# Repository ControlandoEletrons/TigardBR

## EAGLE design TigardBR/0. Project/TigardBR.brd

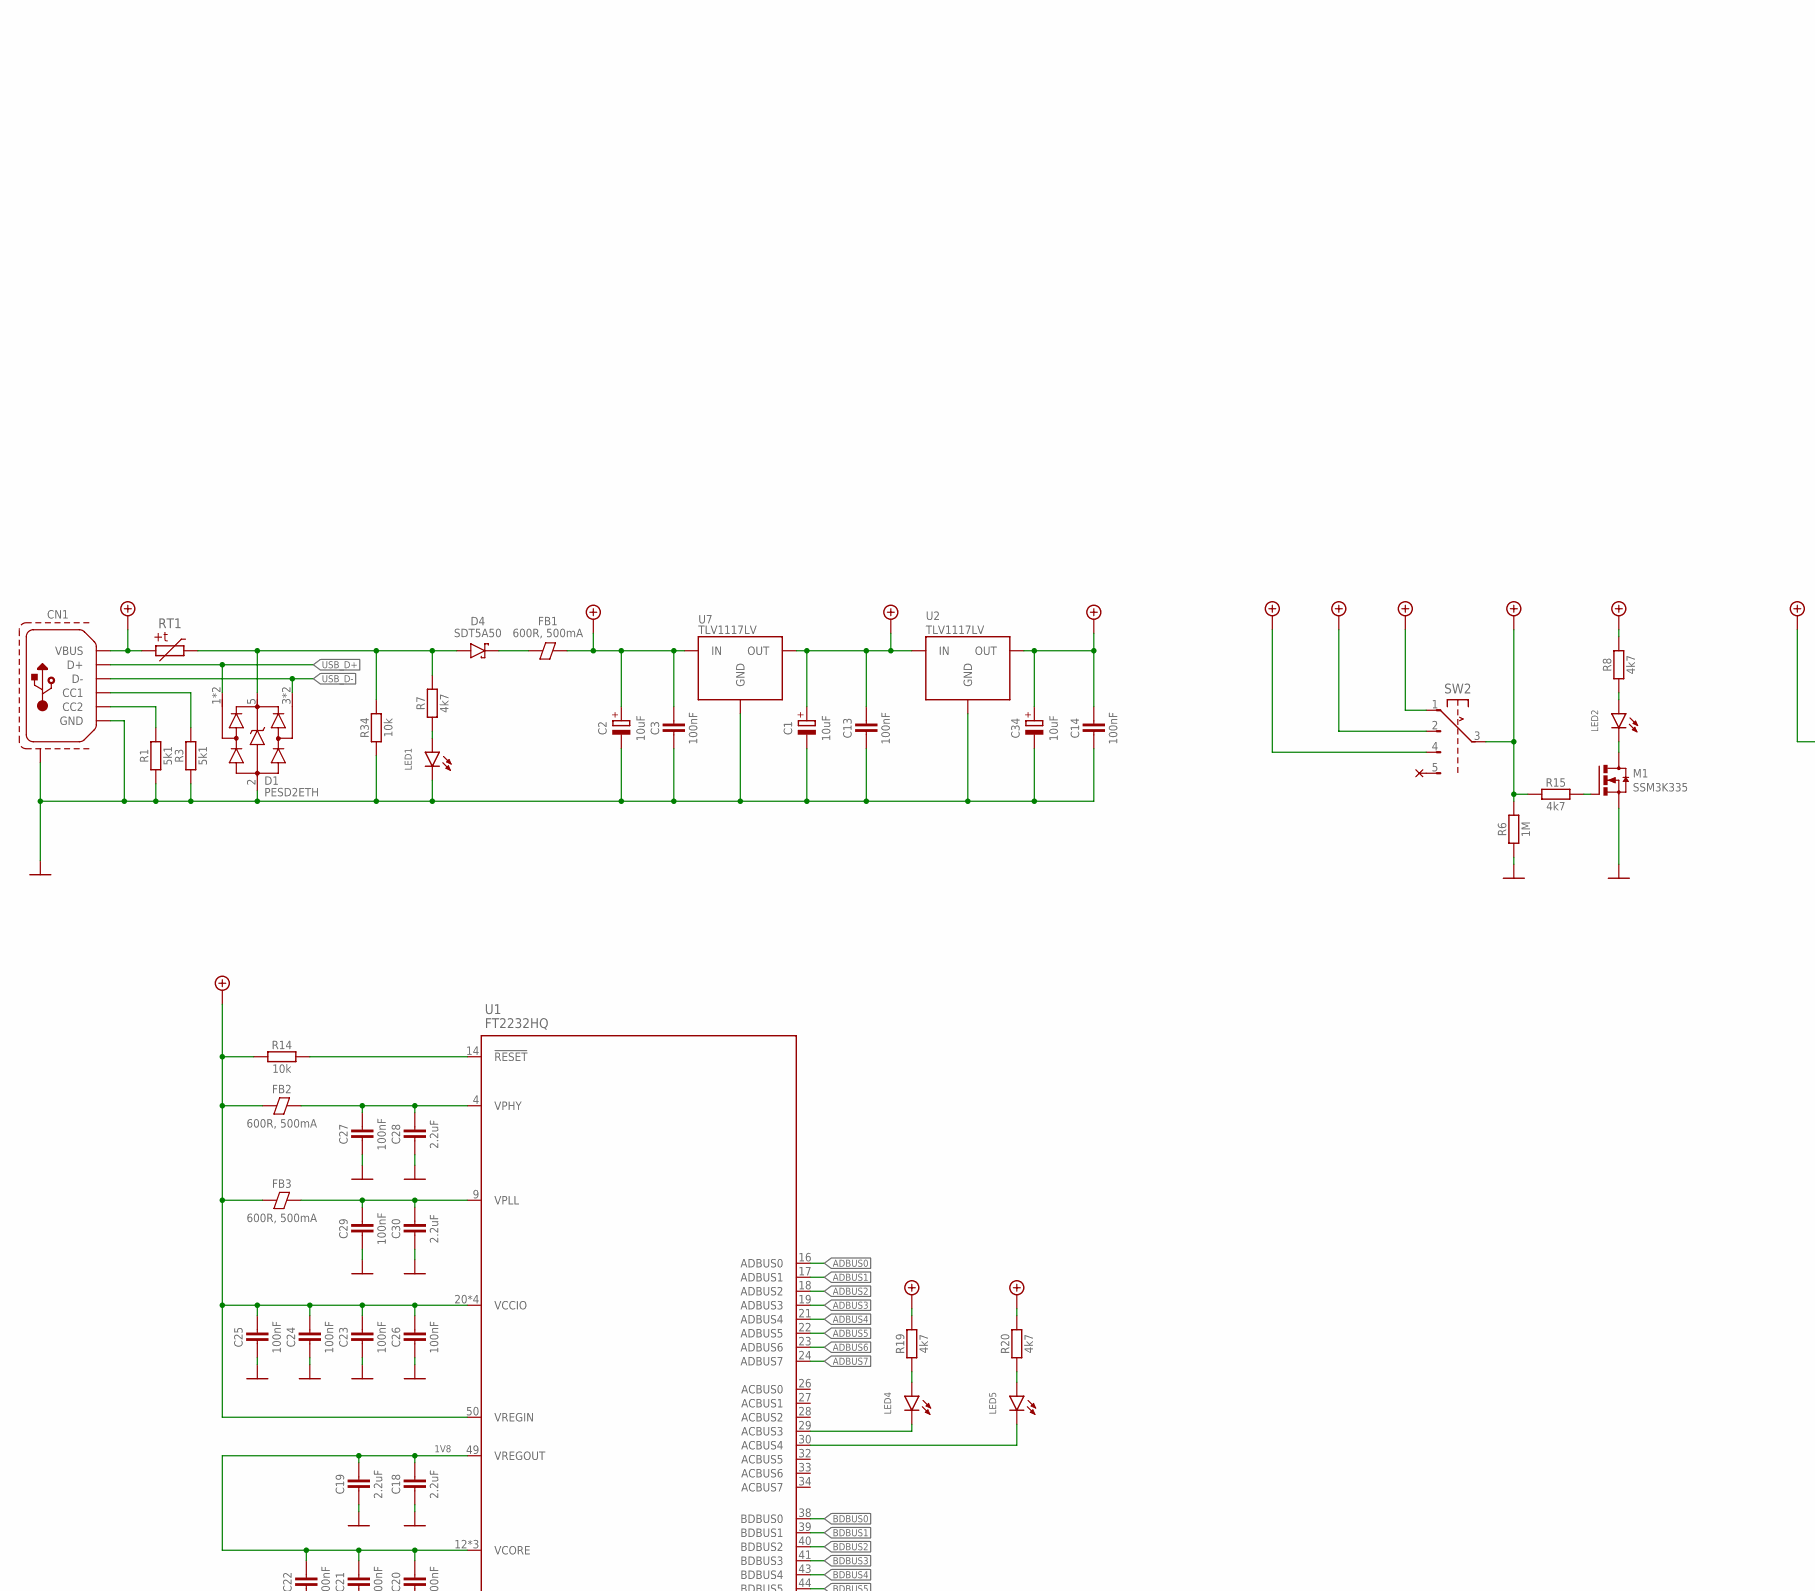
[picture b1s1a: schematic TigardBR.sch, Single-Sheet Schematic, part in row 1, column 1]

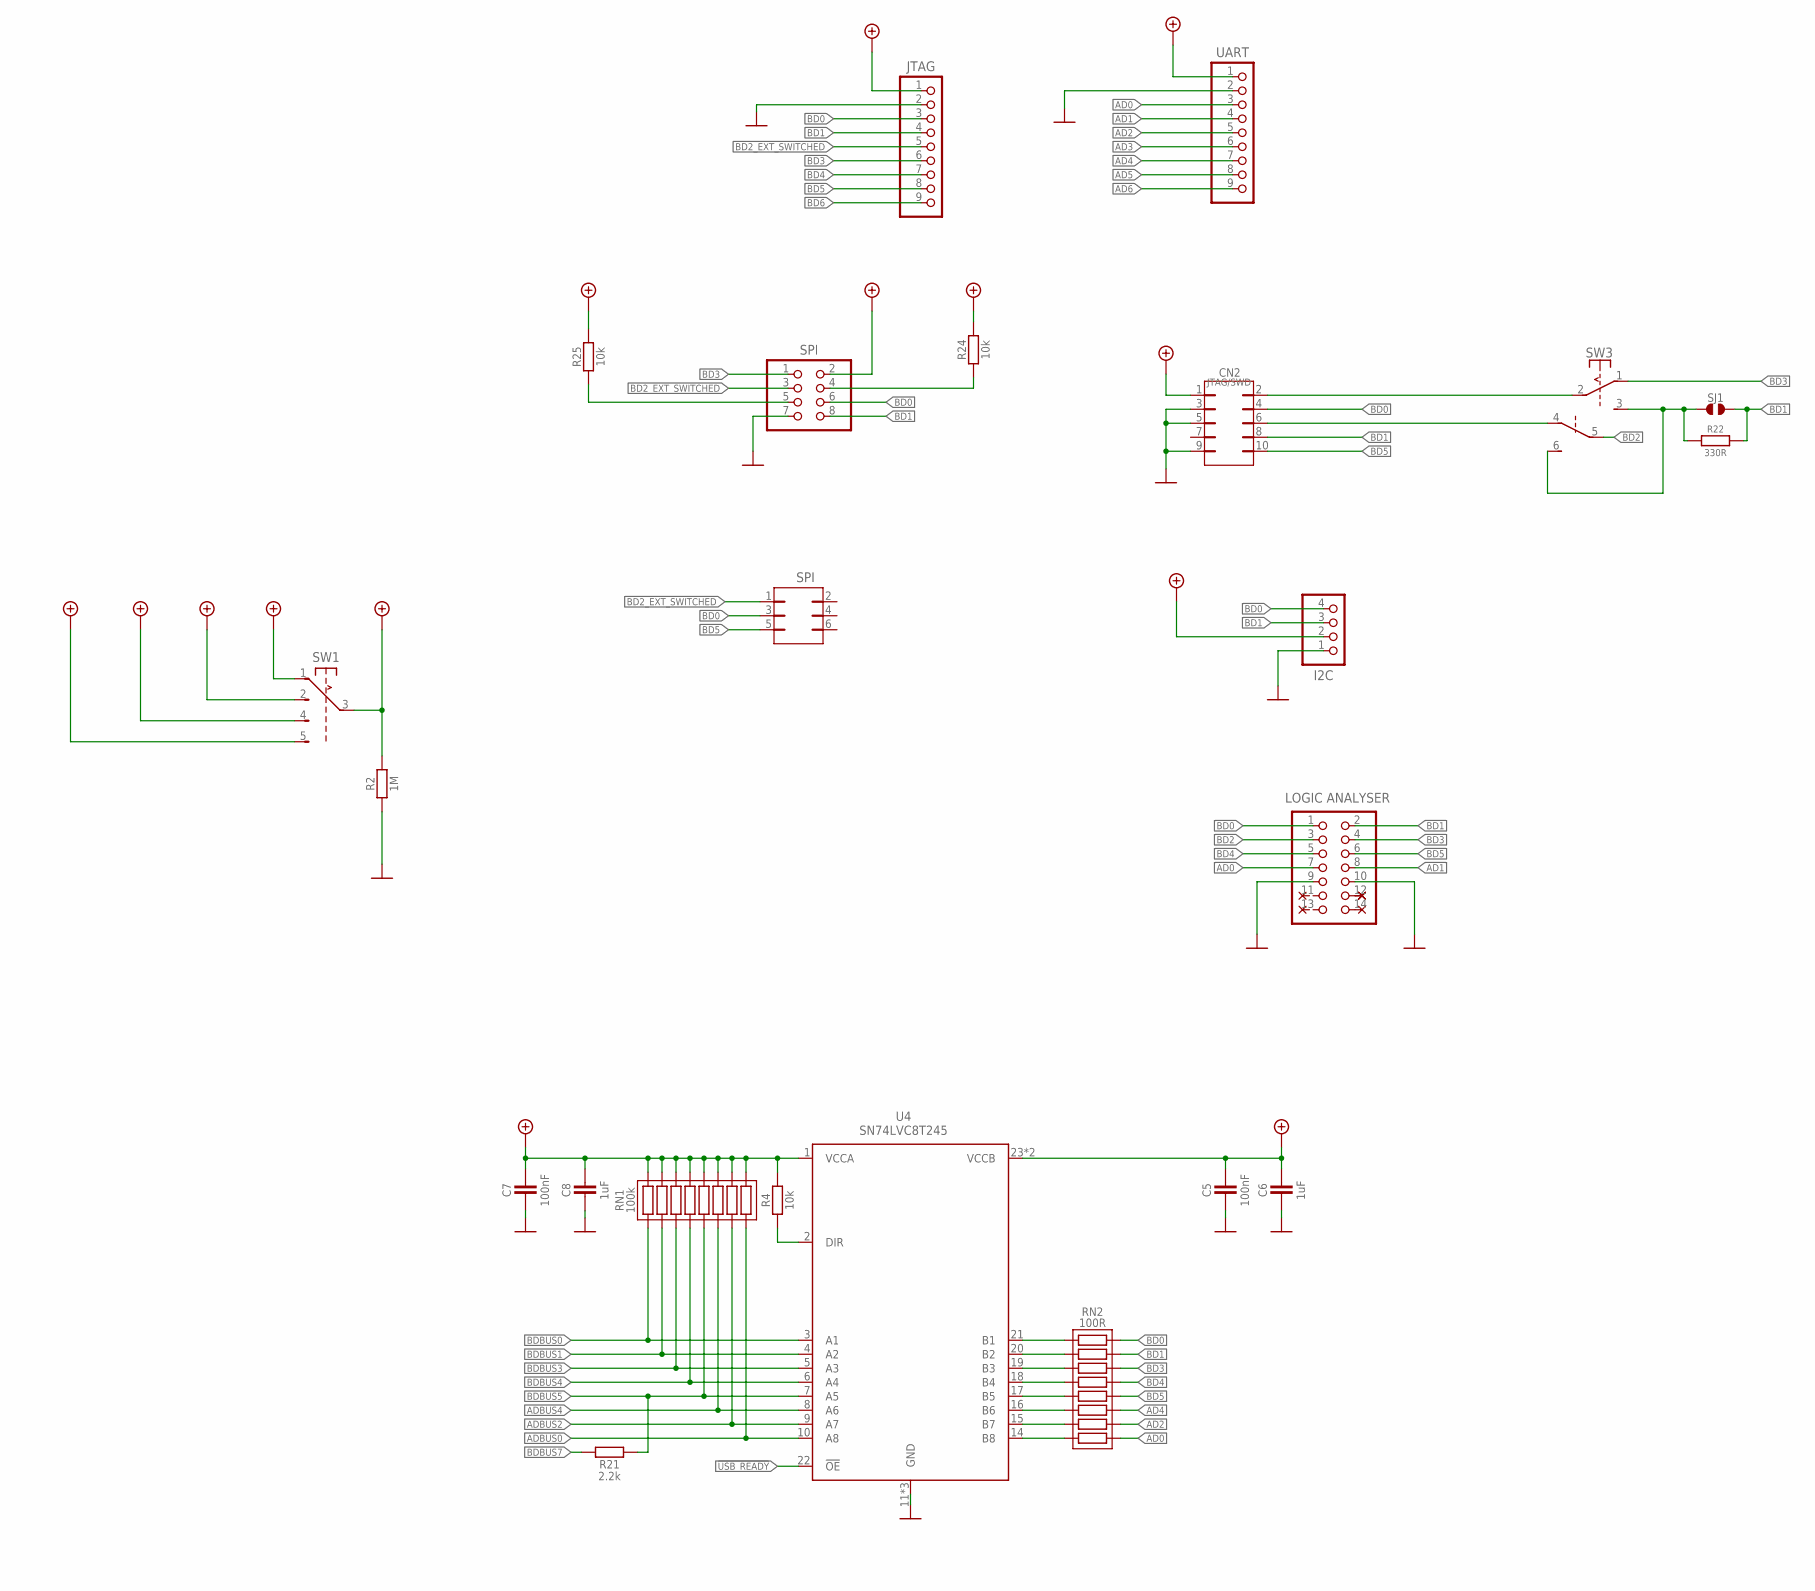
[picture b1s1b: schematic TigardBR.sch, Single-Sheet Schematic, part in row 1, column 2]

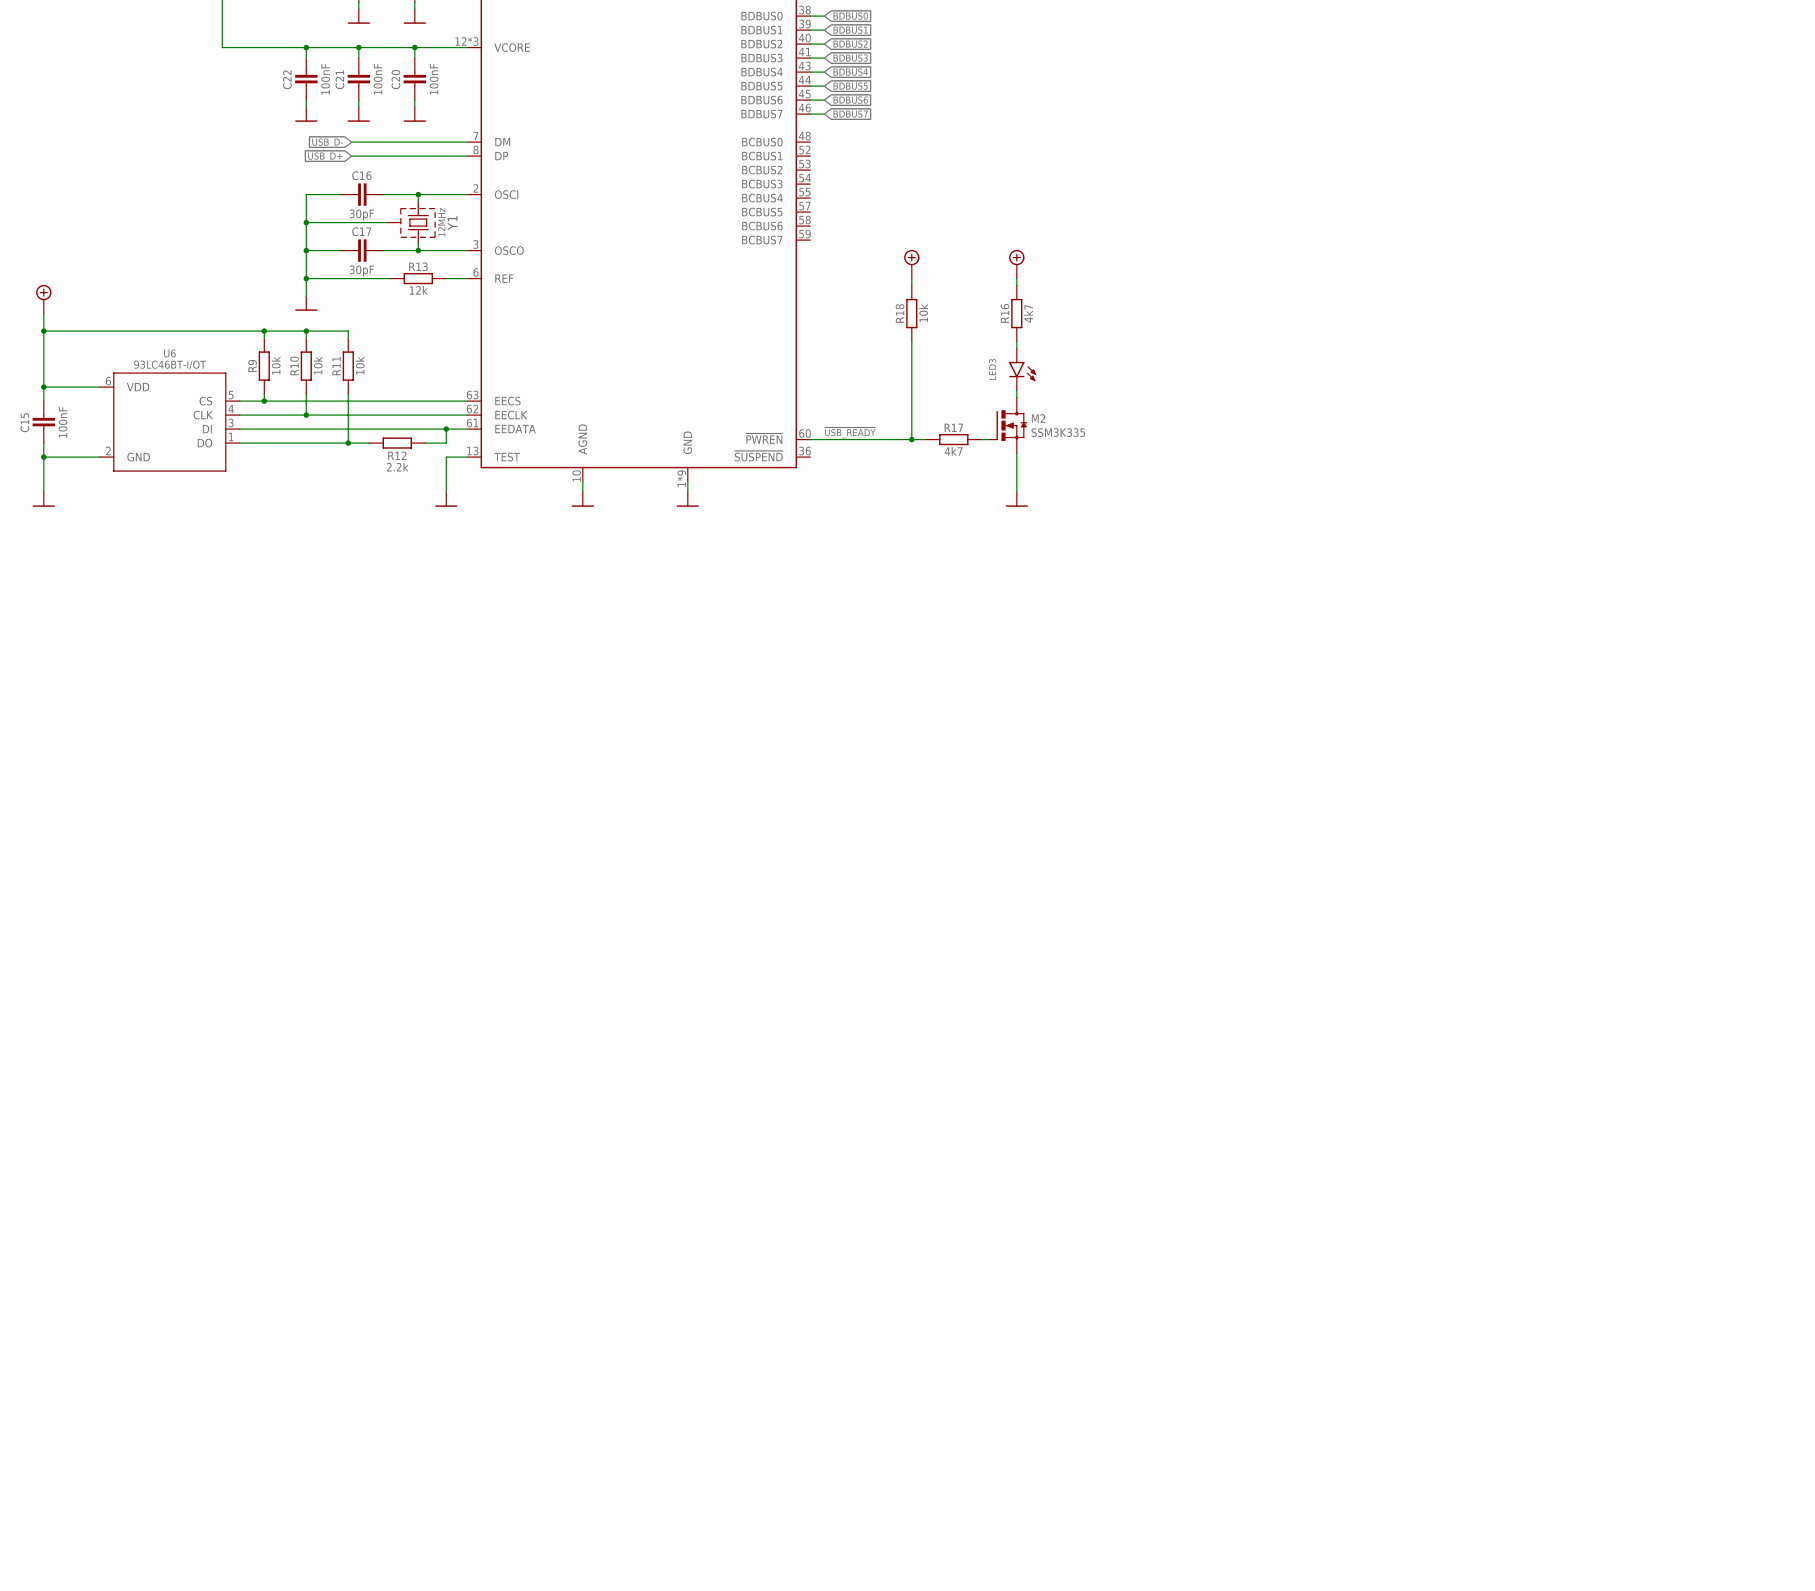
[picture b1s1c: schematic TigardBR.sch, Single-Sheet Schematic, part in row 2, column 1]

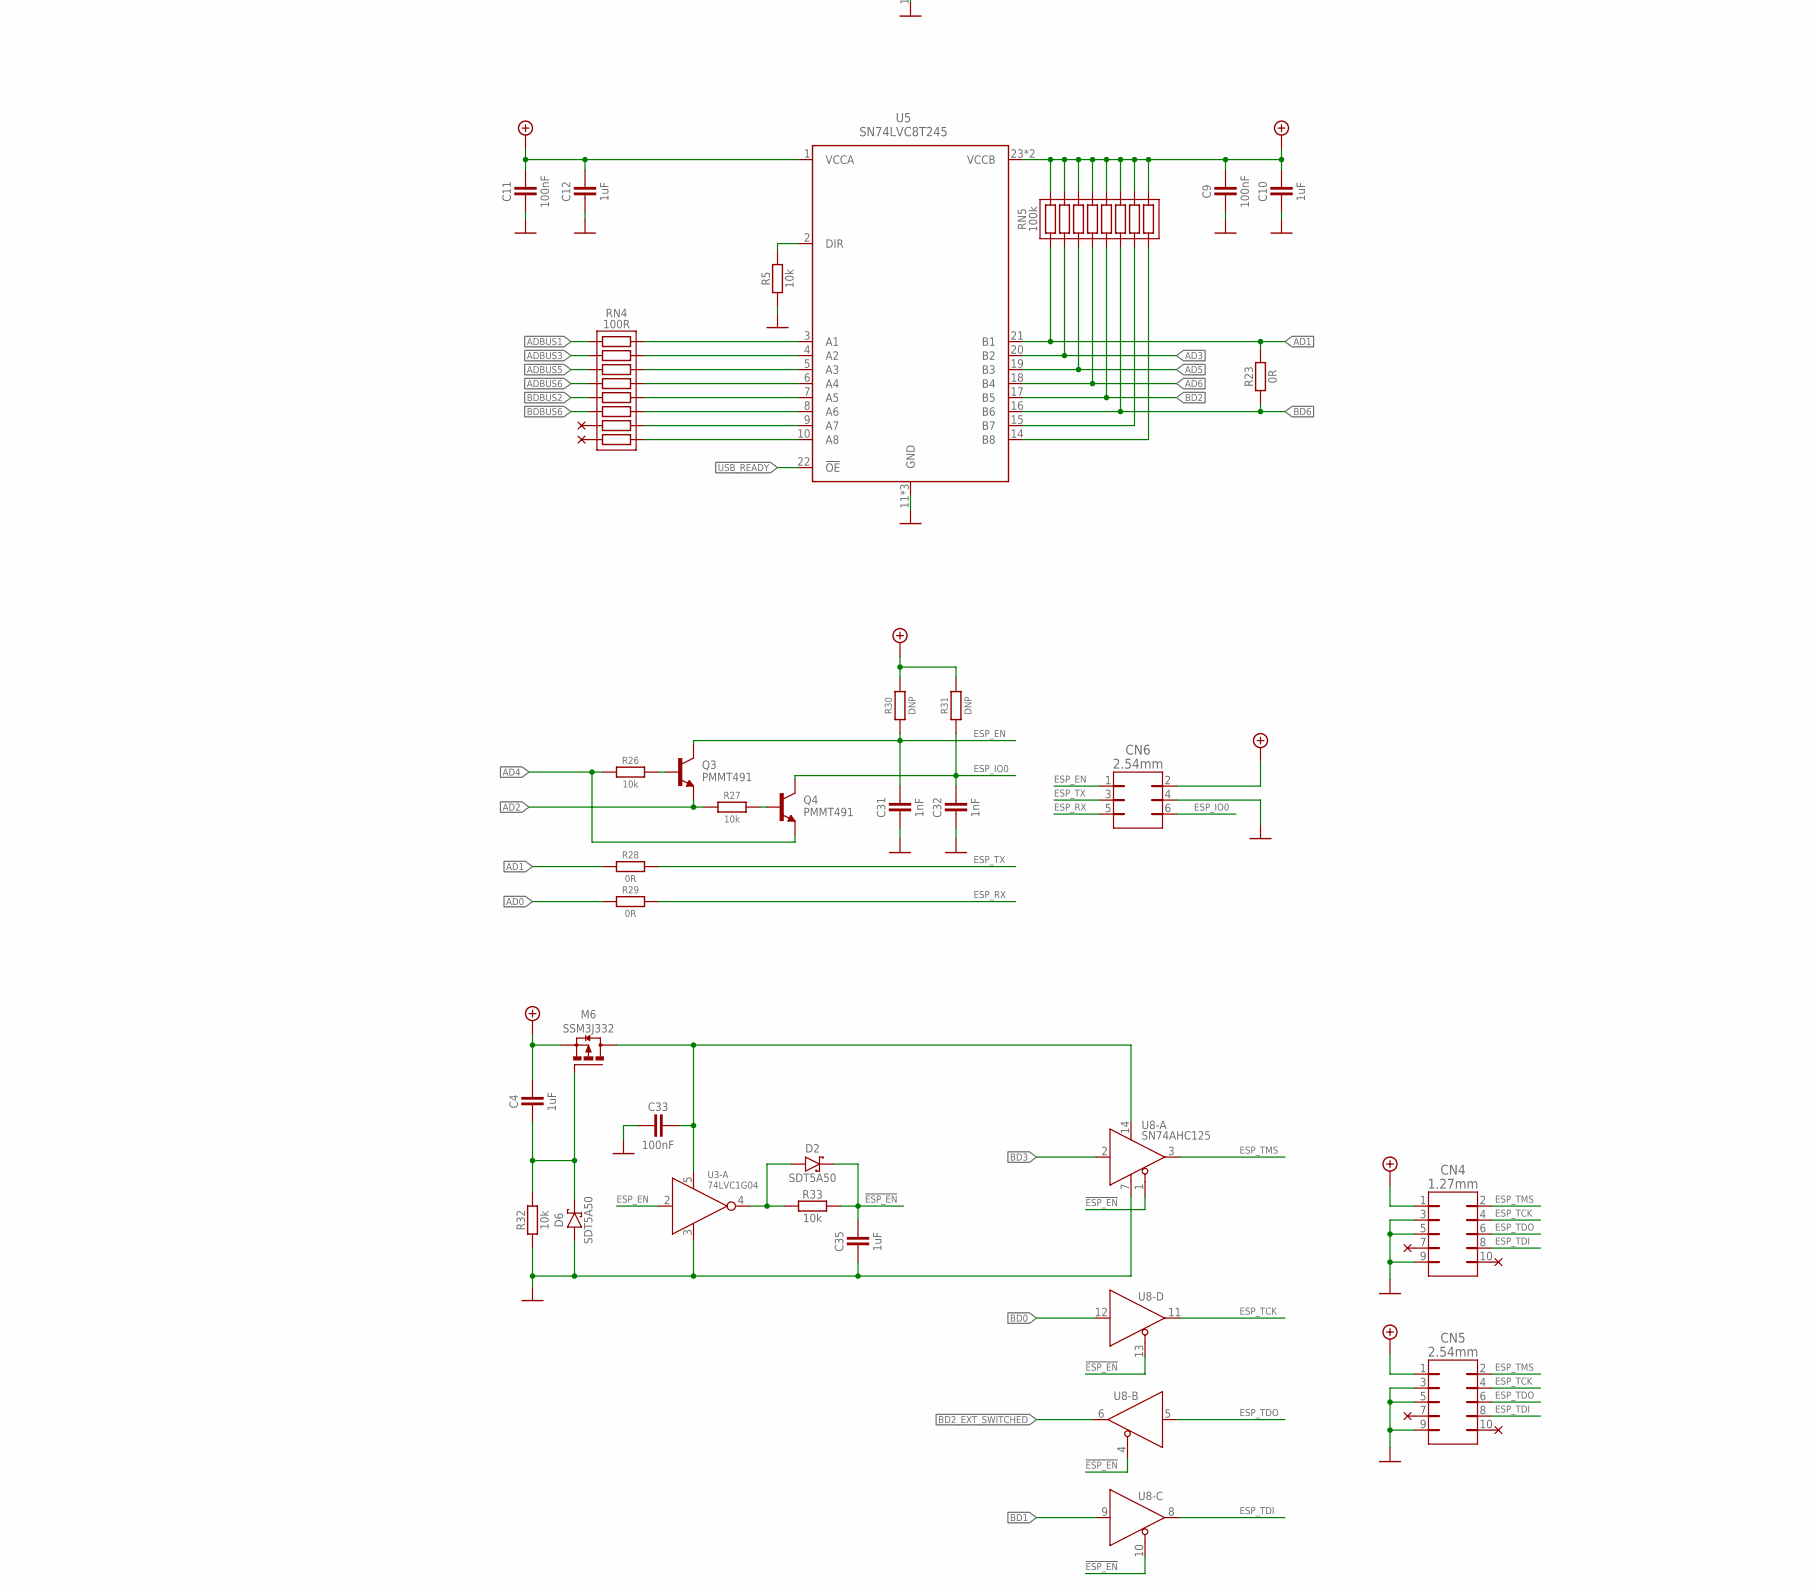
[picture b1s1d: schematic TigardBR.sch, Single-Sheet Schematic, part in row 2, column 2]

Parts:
C1, C2, C34: 10uF; C1206_POL
C3, C5, C7, C9, C11, C13, C14, C15, C20, C21, C22, C23, C24, C25, C26, C27, C29, C33: 100nF; C0603
C4, C6, C8, C10, C12, C35: 1uF; C0603
C16, C17: 30pF; C0603
C18, C19, C28, C30: 2.2uF; C0603
C31, C32: 1nF; C0603
CN1: USB-C-16P
CN2: JTAG/SWD; JTAG-ARM-10P
CN3: I2C; 1X04
CN4: 1.27mm; JTAG-ARM-10P
CN5: 2.54mm; 2X05
CN6: 2.54mm; 2X03
D1: TVS-ARRAY-2; TSOP-6
D2, D4, D6: SDT5A50; DO-214AC
FB1, FB2, FB3: 600R, 500mA; L0603
JP1: JTAG; 1X09
JP2: SPI; 2X04
JP3: UART; 1X09
JP4: LOGIC ANALYSER; 2X07
JP5: SPI; 2X03
LED1: GREEN; L0603G
LED2: BLUE; L0603B
LED3: RED; L0603R
LED4, LED5: YELLOW; L0603Y
M1, M2: SSM3K335; SOT23-3
M6: SSM3J332; SOT23-3
Q3, Q4: PMMT491; SOT23-3
R1, R3: 5k1; R0603
R2, R6: 1M; R0603
R4, R5, R9, R10, R11, R14, R18, R24, R25, R26, R27, R32, R33, R34: 10k; R0603
R7, R8, R15, R16, R17, R19, R20: 4k7; R0603
R12, R21: 2.2k; R0603
R13: 12k; R0603
R22: 330R; R0603
R23, R28, R29: 0R; R0603
R30, R31: DNP; R0603
RN1, RN5: 100k; RN0602
RN2, RN4: 100R; RN0602
RT1: PTC-; F1812
SJ1: 2P-NO; 2P-NO-0603
SW1, SW2: DP4T-; SSSS224100
SW3: DP2T-STRAIGHT-SMD; JS202011SCQN
U1: FT2232HQ; QFN-64
U2, U7: TLV1117LV; SOT-223-3
U3: 74LVC1G04; SOT753-5_(SC-74A)
U4, U5: SN74LVC8T245; TSSOP-24
U6: 93LC46BT-I/OT; SOT23-6
U8: SN74AHC125; SOIC-14
Y1: 12MHz; 3.2MM_2.5MM

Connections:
0V: C1.2 (-), C2.2 (-), C3.2, C5.2, C6.2, C7.2, C8.2, C9.2, C10.2, C11.2, C12.2, C13.2, C14.2, C15.2, C16.2, C17.2, C18.2, C19.2, C20.2, C21.2, C22.2, C23.2, C24.2, C25.2, C26.2, C27.2, C28.2, C29.2, C30.2, C31.2, C32.2, C33.2, C34.2 (-), C35.2, CN1.A1_B12 (GND), CN1.B1_A12 (GND), CN1.S1 (CHASSI), CN1.S2 (CHASSI), CN1.S3 (CHASSI), CN1.S4 (CHASSI), CN2.3 (GND), CN2.5 (GND2), CN2.9 (GND3), CN3.1, CN4.3 (GND), CN4.5 (GND2), CN4.9 (GND3), CN5.3, CN5.5, CN5.9, CN6.4, D1.2 (GND), D6.2 (A), JP1.2, JP2.7, JP3.2, JP4.9, JP4.10, LED1.K, M1.2 (S), M2.2 (S), R1.1, R2.1, R3.1, R5.2, R6.1, R13.2, R32.1, R34.1, U1.1 (GND), U1.5 (GND), U1.10 (AGND), U1.11 (GND), U1.13 (TEST), U1.15 (GND), U1.25 (GND), U1.35 (GND), U1.47 (GND), U1.51 (GND), U1.TP (GND), U2.1 (GND), U3.3 (VSS), U4.11 (GND), U4.12 (GND), U4.13 (GND), U5.11 (GND), U5.12 (GND), U5.13 (GND), U6.2 (GND), U7.1 (GND), U8.7 (VSS), Y1.2 (CH), Y1.4 (CH)
1.8V: C14.1, C34.1 (+), SW1.4 (NO2), SW2.4 (NO2), U2.2 (OUT), U2.4 (OUT)
1V8: C18.1, C19.1, C20.1, C21.1, C22.1, U1.12 (VCORE), U1.37 (VCORE), U1.49 (VREGOUT), U1.64 (VCORE)
3.3V: C1.1 (+), C7.1, C8.1, C11.1, C12.1, C13.1, C15.1, C23.1, C24.1, C25.1, C26.1, FB2.1, FB3.1, R4.1, R8.2, R9.1, R10.1, R11.1, R14.2, R16.2, R18.1, R19.2, R20.2, RN1.1, RN1.2, RN1.3, RN1.4, RN1.5, RN1.6, RN1.7, RN1.8, SW1.2 (NO1), SW2.2 (NO1), U1.20 (VCCIO), U1.31 (VCCIO), U1.42 (VCCIO), U1.50 (VREGIN), U1.56 (VCCIO), U2.3 (IN), U4.1 (VCCA), U5.1 (VCCA), U6.6 (VDD), U7.2 (OUT), U7.4 (OUT)
5.0V: C2.1 (+), C3.1, FB1.2, SW1.1 (NC), SW2.1 (NC), U7.3 (IN)
!ESP_EN: C35.1, D2.1 (K), R33.2, U8.1 (!OE), U8.4 (!OE), U8.10 (!OE), U8.13 (!OE)
!USB_READY: R17.1, R18.2, U1.60 (!PWREN), U4.22 (!OE), U5.22 (!OE)
AD0: JP3.3, JP4.7, R29.1, RN2.9
AD1: JP3.4, JP4.8, R23.1, R28.1, RN5.16, U5.21 (B1)
AD2: JP3.5, Q3.2 (E), R27.1, RN2.10
AD3: JP3.6, RN5.15, U5.20 (B2)
AD4: JP3.7, Q4.2 (E), R26.1, RN2.11
AD5: JP3.8, RN5.14, U5.19 (B3)
AD6: JP3.9, RN5.13, U5.18 (B4)
ADBUS0: RN1.9, RN5.9, U1.16 (ADBUS0), U4.10 (A8), U5.14 (B8)
ADBUS1: RN4.1, U1.17 (ADBUS1)
ADBUS2: RN1.10, RN5.10, U1.18 (ADBUS2), U4.9 (A7), U5.15 (B7)
ADBUS3: RN4.2, U1.19 (ADBUS3)
ADBUS4: RN1.11, U1.21 (ADBUS4), U4.8 (A6)
ADBUS5: RN4.3, U1.22 (ADBUS5)
ADBUS6: RN4.4, U1.23 (ADBUS6)
ADBUS7: U1.24 (ADBUS7)
BD0: CN2.4 (TCK), CN3.4, JP1.3, JP2.6, JP4.1, JP5.3, RN2.16, U8.12 (A)
BD1: CN2.8 (TDI), CN3.3, JP1.4, JP2.8, JP4.2, R22.2, RN2.15, SJ1.2 (3), U8.9 (A)
BD2: JP4.3, RN5.12, SW3.5 (C), U5.17 (B5)
BD2_EXT_SWITCHED: CN2.6 (TDO), JP1.5, JP2.3, JP5.1, SW3.4 (NC), U8.6 (Y)
BD3: JP1.6, JP2.1, JP4.4, RN2.14, SW3.1 (NC), U8.2 (A)
BD4: JP1.7, JP4.5, RN2.13
BD5: CN2.10 (!RST), JP1.8, JP4.6, JP5.5, RN2.12
BD6: JP1.9, R23.2, RN5.11, U5.16 (B6)
BDBUS0: RN1.16, U1.38 (BDBUS0), U4.3 (A1)
BDBUS1: RN1.15, U1.39 (BDBUS1), U4.4 (A2)
BDBUS2: RN4.5, U1.40 (BDBUS2)
BDBUS3: RN1.14, U1.41 (BDBUS3), U4.5 (A3)
BDBUS4: RN1.13, U1.43 (BDBUS4), U4.6 (A4)
BDBUS5: R21.1, RN1.12, U1.44 (BDBUS5), U4.7 (A5)
BDBUS6: RN4.6, U1.45 (BDBUS6)
BDBUS7: R21.2, U1.46 (BDBUS7)
ESP_EN: C31.1, CN6.1, Q3.3 (C), R30.1, U3.2 (A)
ESP_IO0: C32.1, CN6.6, Q4.3 (C), R31.1
ESP_RX: CN6.5, R29.2
ESP_TCK: CN4.4 (TCK), CN5.4, U8.11 (Y)
ESP_TDI: CN4.8 (TDI), CN5.8, U8.8 (Y)
ESP_TDO: CN4.6 (TDO), CN5.6, U8.5 (A)
ESP_TMS: CN4.2 (TMS), CN5.2, U8.3 (Y)
ESP_TX: CN6.3, R28.2
unnamed: LED2.A, R8.1
unnamed: R4.2, U4.2 (DIR)
unnamed: R5.1, U5.2 (DIR)
unnamed: RN4.16, U5.3 (A1)
unnamed: RN4.15, U5.4 (A2)
unnamed: RN4.14, U5.5 (A3)
unnamed: D4.1 (K), FB1.1
unnamed: RN4.13, U5.6 (A4)
unnamed: RN4.12, U5.7 (A5)
unnamed: RN4.11, U5.8 (A6)
unnamed: RN4.10, U5.9 (A7)
unnamed: RN2.1, U4.21 (B1)
unnamed: RN2.2, U4.20 (B2)
unnamed: RN2.3, U4.19 (B3)
unnamed: RN2.4, U4.18 (B4)
unnamed: RN2.5, U4.17 (B5)
unnamed: RN2.6, U4.16 (B6)
unnamed: RN2.7, U4.15 (B7)
unnamed: RN2.8, U4.14 (B8)
unnamed: LED2.K, M1.3 (D)
unnamed: RN4.9, U5.10 (A8)
unnamed: R9.2, U1.63 (EECS), U6.5 (CS)
unnamed: R10.2, U1.62 (EECLK), U6.4 (CLK)
unnamed: R11.2, R12.2, U6.1 (DO)
unnamed: R12.1, U1.61 (EEDATA), U6.3 (DI)
unnamed: LED1.A, R7.1
unnamed: C16.1, U1.2 (OSCI), Y1.1 (IN)
unnamed: C17.1, U1.3 (OSCO), Y1.3 (OUT)
unnamed: R13.1, U1.6 (REF)
unnamed: R14.1, U1.14 (!RESET)
unnamed: C27.1, C28.1, FB2.2, U1.4 (VPHY)
unnamed: C29.1, C30.1, FB3.2, U1.9 (VPLL)
unnamed: M1.1 (G), R15.2
unnamed: LED3.A, R16.1
unnamed: LED3.K, M2.3 (D)
unnamed: M2.1 (G), R17.2
unnamed: LED4.A, R19.1
unnamed: LED4.K, U1.29 (ACBUS3)
unnamed: CN1.A5 (CC1), R3.2
unnamed: CN1.B5 (CC2), R1.2
unnamed: LED5.K, U1.30 (ACBUS4)
unnamed: LED5.A, R20.1
unnamed: CN2.2 (TMS), SW3.2 (C)
unnamed: JP2.4, R24.1
unnamed: JP2.5, R25.1
unnamed: Q3.1 (B), R26.2
unnamed: Q4.1 (B), R27.2
unnamed: D1.5 (VCC), D4.2 (A), R7.2, R34.2, RT1.1
unnamed: C4.2, D6.1 (K), M6.1 (G), R32.2
unnamed: C33.1, M6.3 (D), U3.5 (VDD), U8.14 (VDD)
unnamed: D2.2 (A), R33.1, U3.4 (Y)
SWDIO: R22.1, SJ1.1, SW3.3 (NO), SW3.6 (NO)
USB_D+: CN1.A6 (D+), CN1.B6 (D+), D1.1 (IO1), D1.6 (IO1), U1.8 (DP)
USB_D-: CN1.A7 (D-), CN1.B7 (D-), D1.3 (IO2), D1.4 (IO2), U1.7 (DM)
VBUS: CN1.A4_B9 (VBUS), CN1.B4_A9 (VBUS), RT1.2
VLOGIC: C4.1, C5.1, C6.1, C9.1, C10.1, M6.2 (S), R2.2, R30.2, R31.2, RN5.1, RN5.2, RN5.3, RN5.4, RN5.5, RN5.6, RN5.7, RN5.8, SW1.3 (C), U4.23 (VCCB), U4.24 (VCCB), U5.23 (VCCB), U5.24 (VCCB)
VTARGET: CN2.1 (VDD), CN3.2, CN4.1 (VDD), CN5.1, CN6.2, JP1.1, JP2.2, JP3.1, R6.2, R15.1, R24.2, R25.2, SW1.5 (NO3), SW2.3 (C)

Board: 2 copper layers, 115 parts (0 on the bottom side), 102 nets, no tracks yet.

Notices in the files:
parts and their libraries:
My-RLC: Copyright (C) 2007, Bob Starr
